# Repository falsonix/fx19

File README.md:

# fx19
Custom mechanical number pad for personal computers

# License information
This work is licensed under a
[Creative Commons Attribution-ShareAlike 4.0 International License][cc-sa].

[![CC SA 4.0][cc-sa-image]][cc-sa]

[cc-sa]: http://creativecommons.org/licenses/by-sa/4.0/
[cc-sa-image]: https://i.creativecommons.org/l/by-sa/4.0/88x31.png
[cc-sa-shield]: https://mirrors.creativecommons.org/presskit/buttons/88x31/svg/by-sa.svg

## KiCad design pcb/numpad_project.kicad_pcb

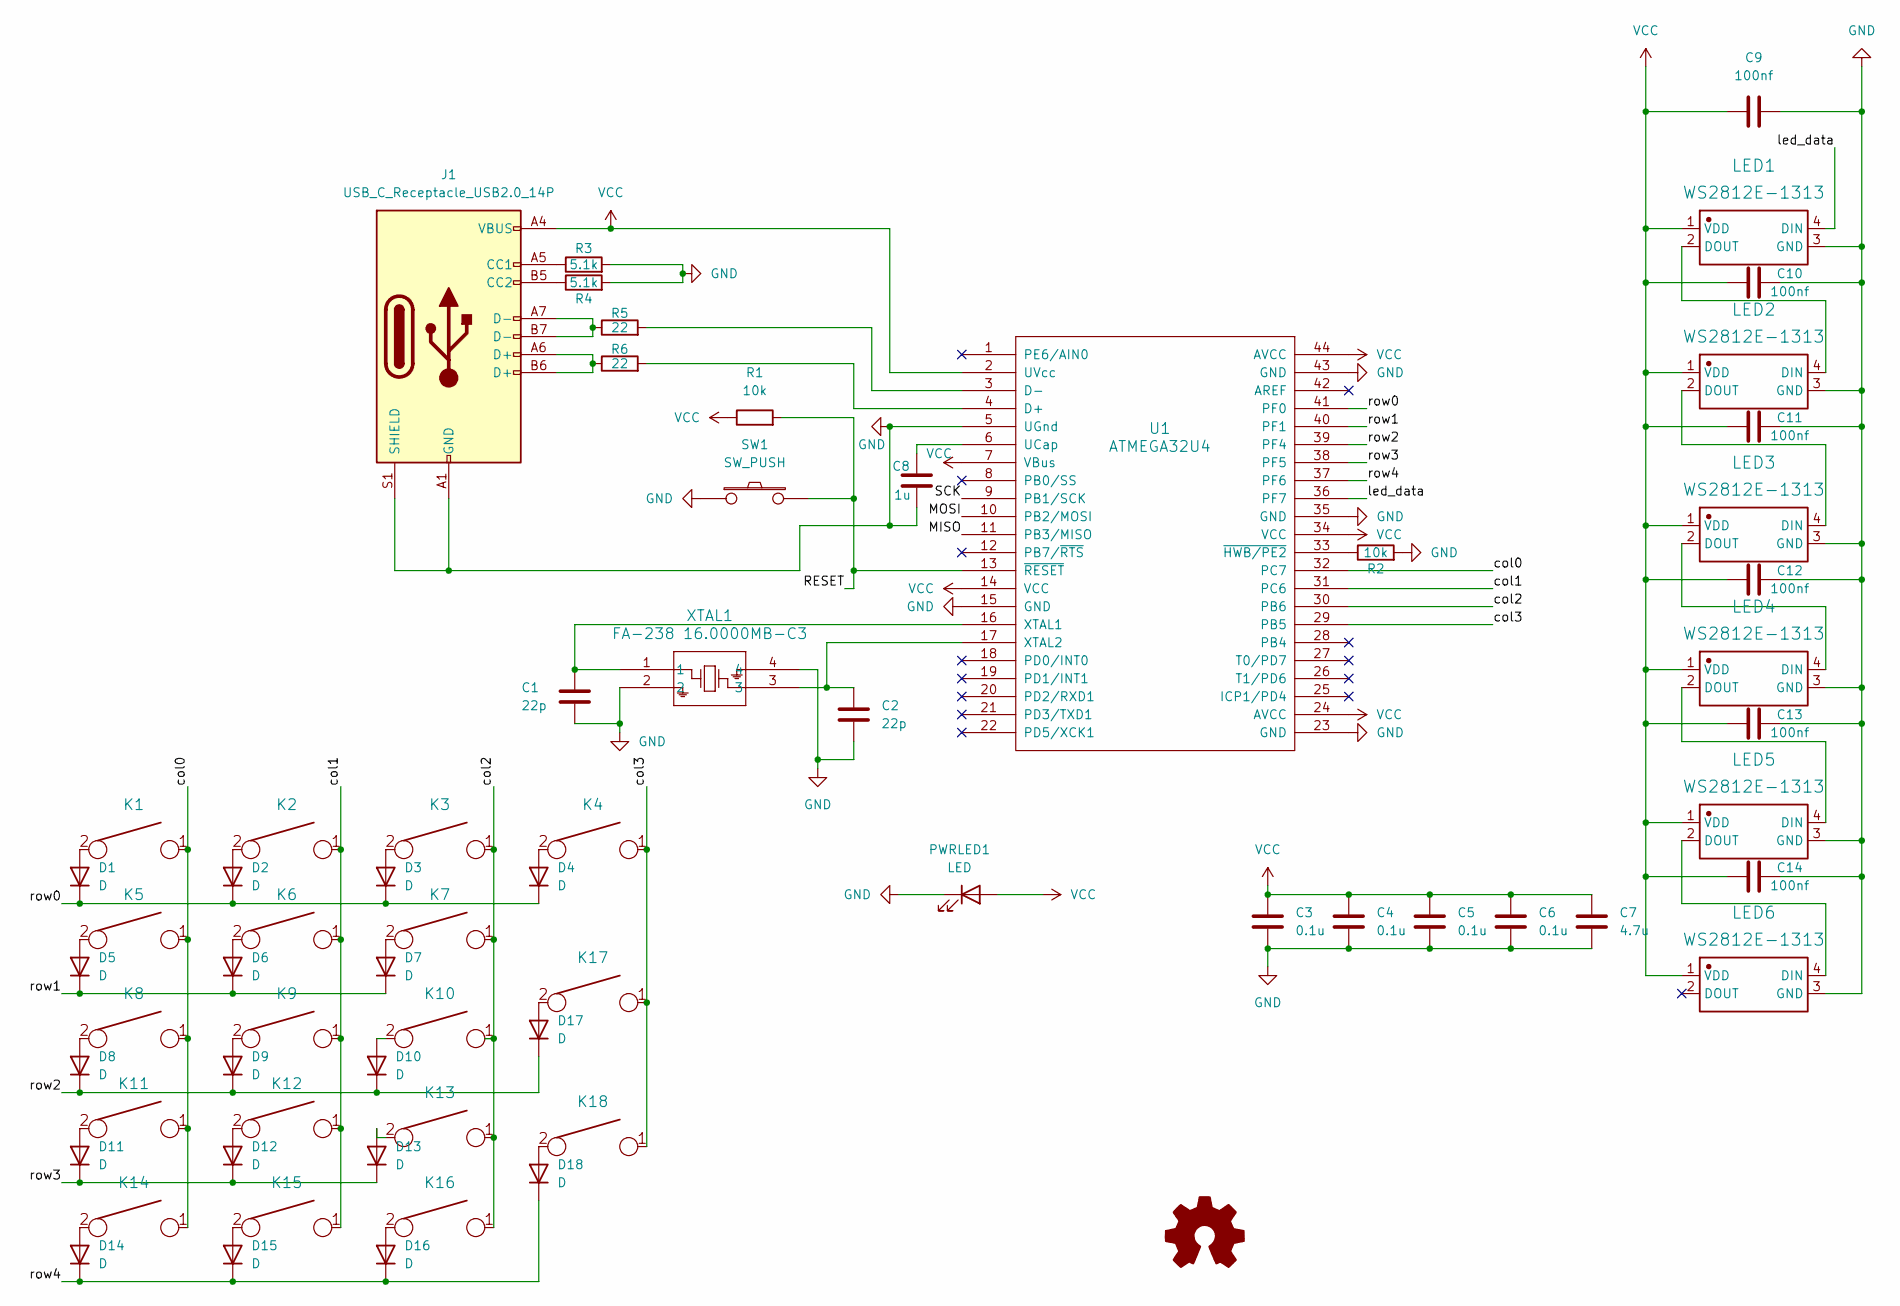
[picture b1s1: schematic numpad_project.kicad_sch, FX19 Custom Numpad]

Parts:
C1, C2: 22p; C_0805_2012Metric_Pad1.18x1.45mm_HandSolder
C3, C4, C5, C6: 0.1u; C_0805_2012Metric_Pad1.18x1.45mm_HandSolder
C7: 4.7u; C_0805_2012Metric_Pad1.18x1.45mm_HandSolder
C8: 1u; C_0805_2012Metric_Pad1.18x1.45mm_HandSolder
C9, C10, C11, C12, C13, C14: 100nf; C_0805_2012Metric_Pad1.18x1.45mm_HandSolder
D1, D2, D3, D4, D5, D6, D7, D8, D9, D10, D11, D12, D13, D14, D15, D16, D17, D18: D; D_SOD123_axial
J1: USB_C_Receptacle_USB2.0_14P; USB_C_Receptacle_HRO_TYPE-C-31-M-12
K1, K2, K3, K4, K5, K6, K7, K8, K9, K10, K11, K12, K13, K14, K15, K16, K17, K18: KEYSW; Mx_Alps_100
LED1, LED2, LED3, LED4, LED5, LED6: WS2812E-1313; LED-SMD_4P-L1.3-W1.3-P0.80_WS2812E-1313; Manufacturer Part WS2812E-1313
PWRLED1: LED; LED_1206_3216Metric_Pad1.42x1.75mm_HandSolder
R1, R2: 10k; R_0805_2012Metric_Pad1.20x1.40mm_HandSolder
R3, R4: 5.1k; R_0805_2012Metric_Pad1.20x1.40mm_HandSolder
R5, R6: 22; R_0805_2012Metric_Pad1.20x1.40mm_HandSolder
SW1: SW_PUSH; SW_SPST_TL3342
U1: ATMEGA32U4; TQFP-44_10x10mm_P0.8mm
XTAL1: FA-238 16.0000MB-C3; Crystal_SMD_SeikoEpson_FA238-4Pin_3.2x2.5mm_HandSoldering

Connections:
/MISO: U1.11 (PB3/MISO); also elsewhere on the board
/MOSI: U1.10 (PB2/MOSI); also elsewhere on the board
/RESET: R1.2, SW1.2, U1.13 (~RESET); also elsewhere on the board
/SCK: U1.9 (PB1/SCK); also elsewhere on the board
/col0: K1.1, K5.1, K8.1, K11.1, K14.1, U1.32 (PC7)
/col1: K2.1, K6.1, K9.1, K12.1, K15.1, U1.31 (PC6)
/col2: K3.1, K7.1, K10.1, K13.1, K16.1, U1.30 (PB6)
/col3: K4.1, K17.1, K18.1, U1.29 (PB5)
/led_data: LED1.4 (DIN), U1.36 (PF7)
/row0: D1.1 (K), D2.1 (K), D3.1 (K), D4.1 (K), U1.41 (PF0)
/row1: D5.1 (K), D6.1 (K), D7.1 (K), U1.40 (PF1)
/row2: D8.1 (K), D9.1 (K), D10.1 (K), D17.1 (K), U1.39 (PF4)
/row3: D11.1 (K), D12.1 (K), D13.1 (K), U1.38 (PF5)
/row4: D14.1 (K), D15.1 (K), D16.1 (K), D18.1 (K), U1.37 (PF6)
GND: C1.2, C2.2, C3.2, C4.2, C5.2, C6.2, C7.2, C8.2, C9.2, C10.2, C11.2, C12.2, C13.2, C14.2, J1.A1 (GND), J1.A12 (GND), J1.B1 (GND), J1.B12 (GND), J1.S1 (SHIELD), LED1.3 (GND), LED2.3 (GND), LED3.3 (GND), LED4.3 (GND), LED5.3 (GND), LED6.3 (GND), PWRLED1.1 (K), R2.2, R3.2, R4.2, SW1.1, U1.5 (UGnd), U1.15 (GND), U1.23 (GND), U1.35 (GND), U1.43 (GND), XTAL1.2, XTAL1.4
unnamed: D1.2 (A), K1.2
unnamed: D2.2 (A), K2.2
unnamed: D3.2 (A), K3.2
unnamed: D4.2 (A), K4.2
unnamed: D5.2 (A), K5.2
unnamed: D6.2 (A), K6.2
unnamed: D7.2 (A), K7.2
unnamed: D8.2 (A), K8.2
unnamed: D9.2 (A), K9.2
unnamed: D10.2 (A), K10.2
unnamed: D11.2 (A), K11.2
unnamed: D12.2 (A), K12.2
unnamed: D13.2 (A), K13.2
unnamed: D14.2 (A), K14.2
unnamed: D15.2 (A), K15.2
unnamed: D16.2 (A), K16.2
unnamed: D17.2 (A), K17.2
unnamed: D18.2 (A), K18.2
unnamed: J1.A5 (CC1), R3.1
unnamed: J1.B5 (CC2), R4.1
unnamed: J1.A6 (D+), J1.B6 (D+), R6.1
unnamed: J1.A7 (D-), J1.B7 (D-), R5.1
unnamed: LED1.2 (DOUT), LED2.4 (DIN)
unnamed: LED2.2 (DOUT), LED3.4 (DIN)
unnamed: LED3.2 (DOUT), LED4.4 (DIN)
unnamed: LED4.2 (DOUT), LED5.4 (DIN)
unnamed: LED5.2 (DOUT), LED6.4 (DIN)
unnamed: R6.2, U1.4 (D+)
unnamed: R5.2, U1.3 (D-)
unnamed: C8.1, U1.6 (UCap)
unnamed: C1.1, U1.16 (XTAL1), XTAL1.1
unnamed: C2.1, U1.17 (XTAL2), XTAL1.3
unnamed: R2.1, U1.33 (~HWB/PE2)
VCC: C3.1, C4.1, C5.1, C6.1, C7.1, C9.1, C10.1, C11.1, C12.1, C13.1, C14.1, J1.A4 (VBUS), J1.A9 (VBUS), J1.B4 (VBUS), J1.B9 (VBUS), LED1.1 (VDD), LED2.1 (VDD), LED3.1 (VDD), LED4.1 (VDD), LED5.1 (VDD), LED6.1 (VDD), PWRLED1.2 (A), R1.1, U1.2 (UVcc), U1.7 (VBus), U1.14 (VCC), U1.24 (AVCC), U1.34 (VCC), U1.44 (AVCC); also elsewhere on the board

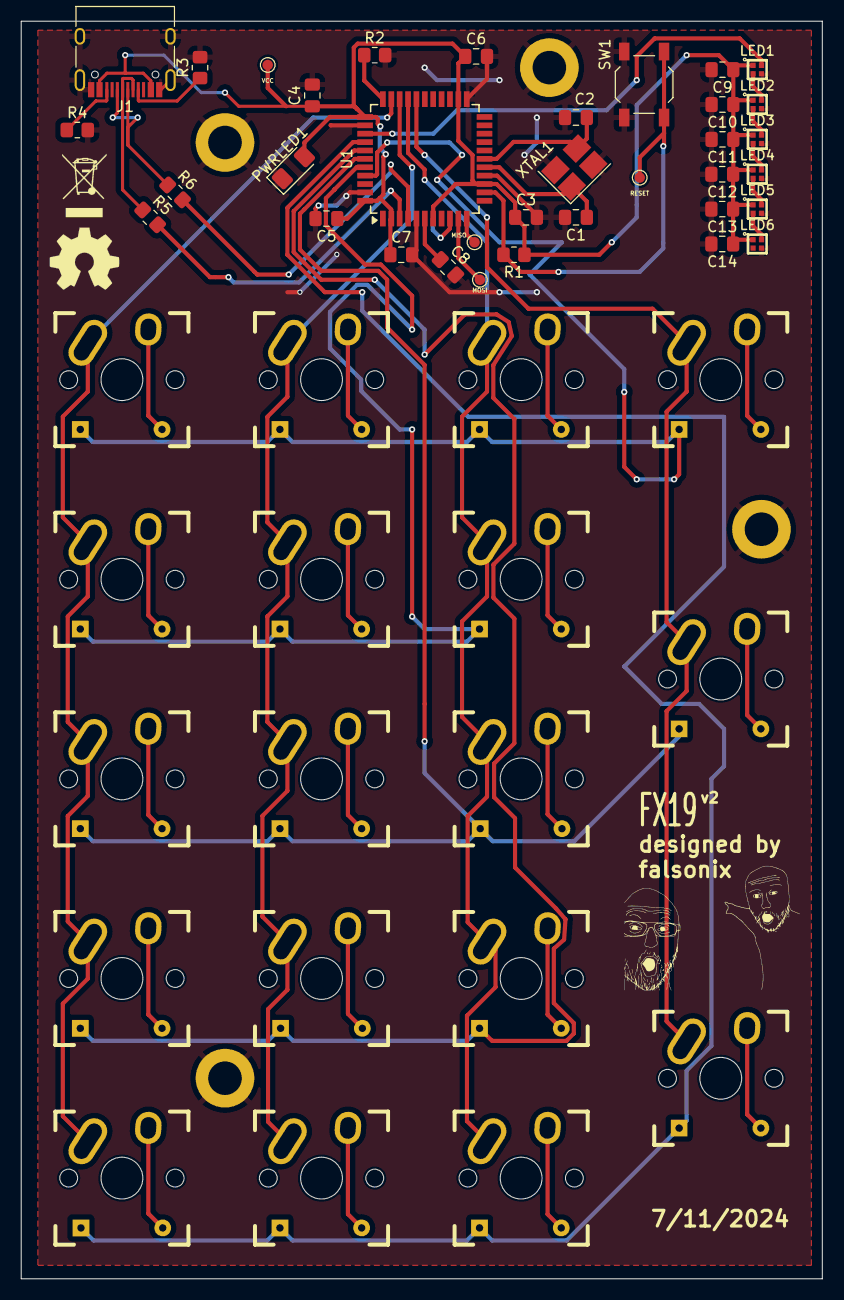
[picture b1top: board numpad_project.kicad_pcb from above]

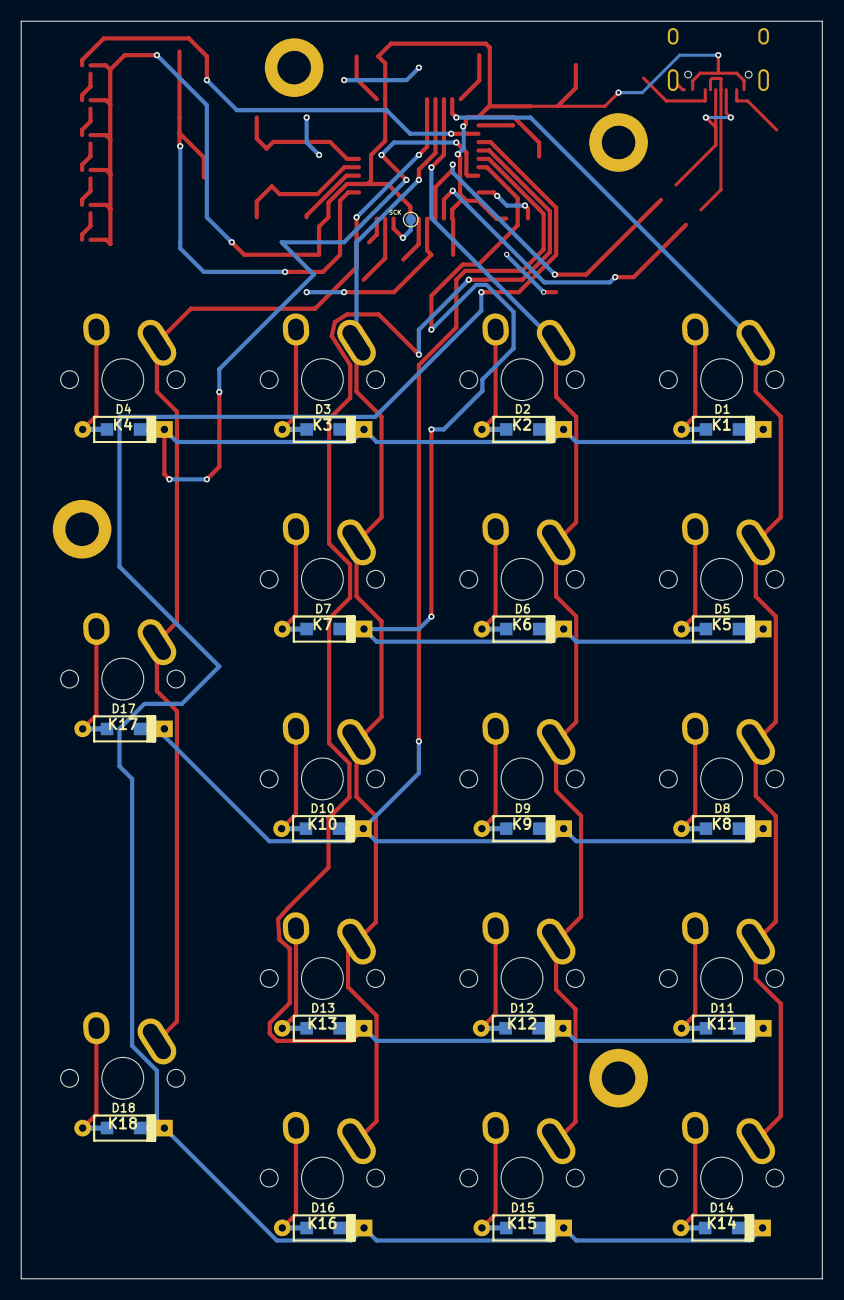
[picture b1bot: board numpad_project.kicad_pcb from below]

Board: 2 copper layers, 76.5 x 120.0 mm, 72 parts (19 on the bottom side), 49 nets.

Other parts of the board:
MISO: TestPoint_Pad_D1.0mm
MOSI: TestPoint_Pad_D1.0mm
RESET: TestPoint_Pad_D1.0mm
SCK: TestPoint_Pad_D1.0mm
VCC: TestPoint_Pad_D1.0mm

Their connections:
/MISO: MISO.1; also elsewhere on the board
/MOSI: MOSI.1; also elsewhere on the board
/RESET: RESET.1; also elsewhere on the board
/SCK: SCK.1; also elsewhere on the board
VCC: VCC.1; also elsewhere on the board

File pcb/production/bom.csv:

Designator,Footprint,Quantity,Value,LCSC Part #
"C1, C2",0805,2,22p,
"C10, C11, C12, C13, C14, C9",0805,6,100nf,
"C3, C4, C5, C6",0805,4,0.1u,
C7,0805,1,4.7u,
C8,0805,1,1u,
"D1, D10, D11, D12, D13, D14, D15, D16, D17, D18, D2, D3, D4, D5, D6, D7, D8, D9",D_SOD123_axial,18,D,
J1,USB_C_Receptacle_HRO_TYPE-C-31-M-12,1,USB_C_Receptacle_USB2.0_14P,
"K1, K10, K11, K12, K13, K14, K15, K16, K17, K18, K2, K3, K4, K5, K6, K7, K8, K9",Mx_Alps_100,18,KEYSW,
"LED1, LED2, LED3, LED4, LED5, LED6",LED-SMD_4P-L1.3-W1.3-P0.80_WS2812E-1313,6,WS2812E-1313,
PWRLED1,1206,1,LED,
"R1, R2",0805,2,10k,
"R3, R4",0805,2,5.1k,
"R5, R6",0805,2,22,
SW1,SW_SPST_TL3342,1,SW_PUSH,
U1,TQFP-44_10x10mm_P0.8mm,1,ATMEGA32U4,
XTAL1,Crystal_SMD_SeikoEpson_FA238-4Pin_3.2x2.5mm_HandSoldering,1,FA-238 16.0000MB-C3,

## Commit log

2024-07-11 create part of file structure
2024-07-11 add production files
2024-07-11 Create LICENSE
2024-07-11 add printing files
2024-07-11 add more printing files
2024-07-11 add image
2024-07-11 Rename fx19-enclosure v45.png to fx19-enclosure-v45.png
2024-07-11 add source files
